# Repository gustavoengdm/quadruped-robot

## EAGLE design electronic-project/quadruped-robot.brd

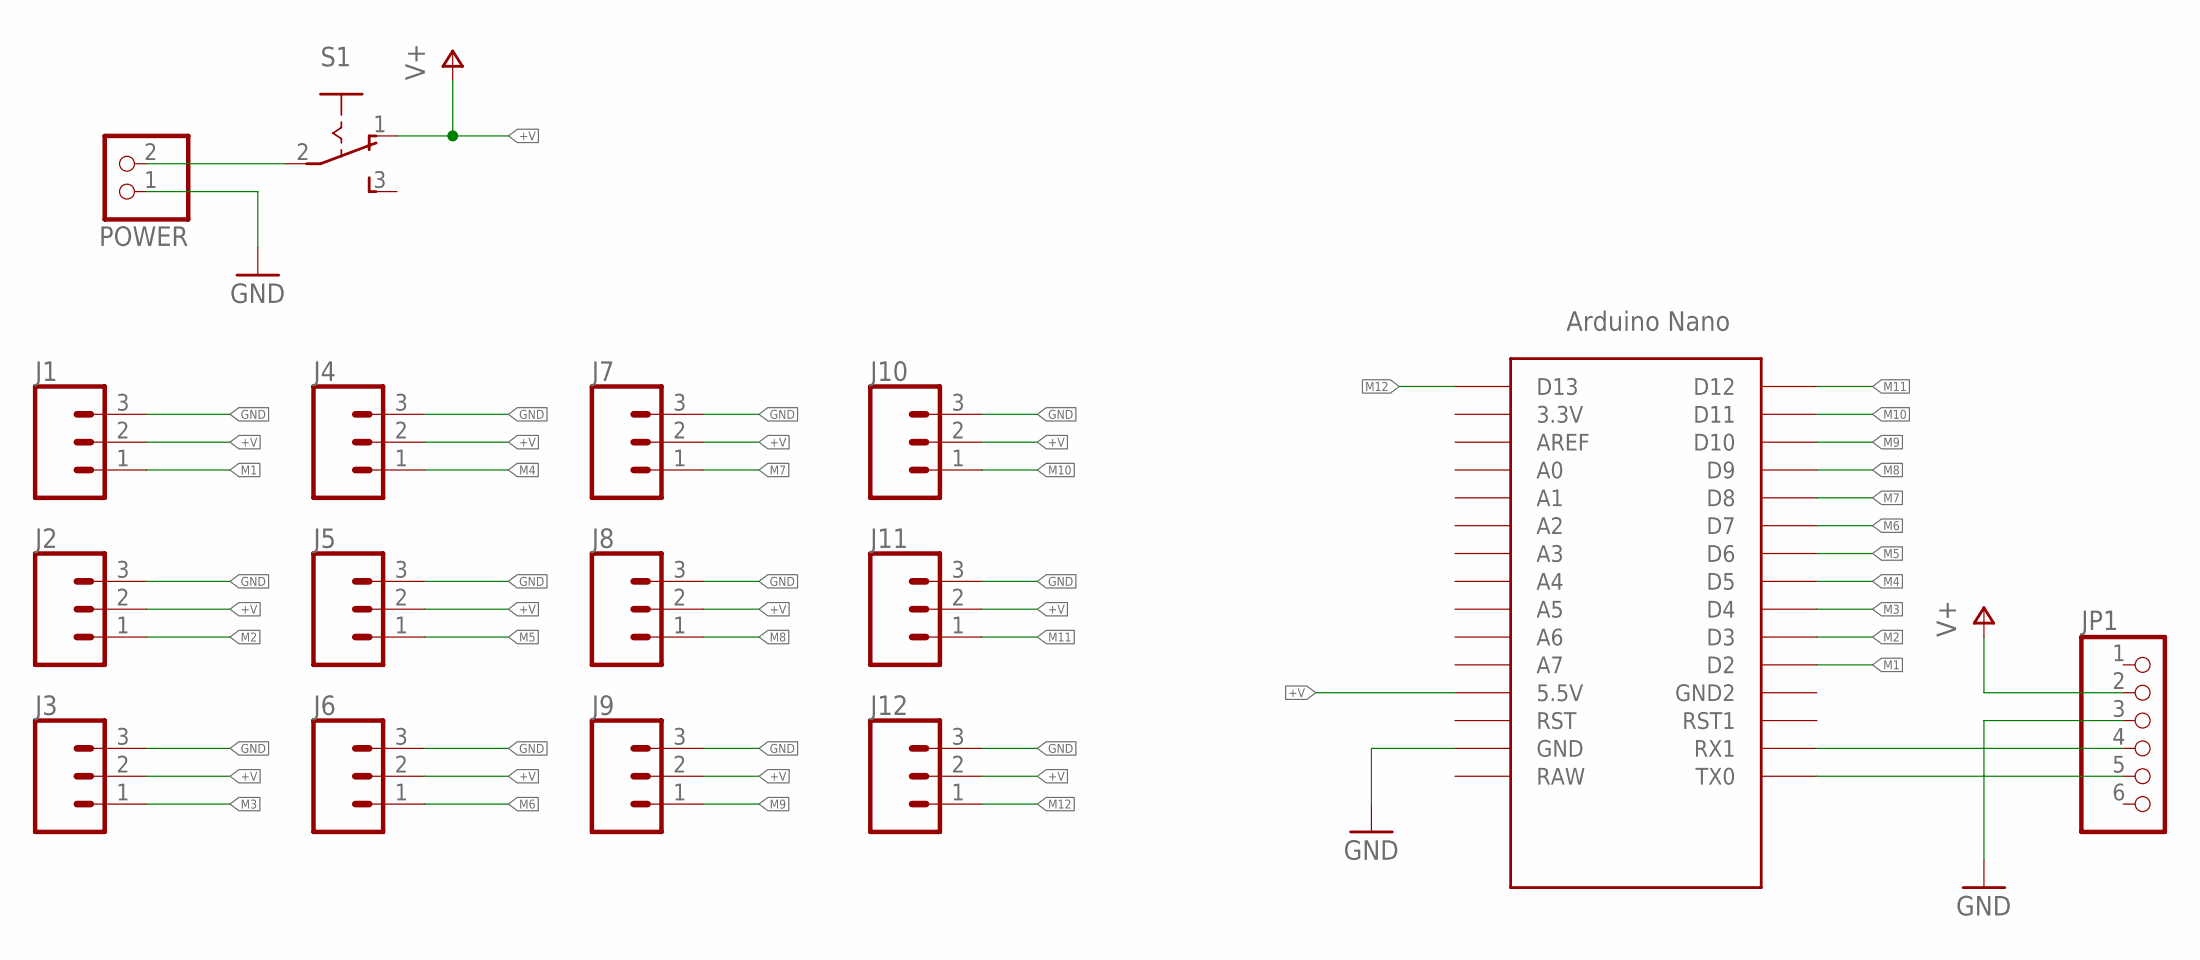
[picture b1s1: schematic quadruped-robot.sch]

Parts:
J1, J2, J3, J4, J5, J6, J7, J8, J9, J10, J11, J12: CONN_03; 1X03
JP1: PINHD-1X6; 1X06
POWER: PINHD-1X2; 1X02
S1: 255SB
U$1: NANO

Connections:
+V: J1.2, J2.2, J3.2, J4.2, J5.2, J6.2, J7.2, J8.2, J9.2, J10.2, J11.2, J12.2, JP1.2, S1.1 (O), U$1.5V (5.5V)
GND: J1.3, J2.3, J3.3, J4.3, J5.3, J6.3, J7.3, J8.3, J9.3, J10.3, J11.3, J12.3, JP1.3, POWER.1, U$1.GND
M1: J1.1, U$1.D2
M2: J2.1, U$1.D3
M3: J3.1, U$1.D4
M4: J4.1, U$1.D5
M5: J5.1, U$1.D6
M6: J6.1, U$1.D7
M7: J7.1, U$1.D8
M8: J8.1, U$1.D9
M9: J9.1, U$1.D10
M10: J10.1, U$1.D11
M11: J11.1, U$1.D12
M12: J12.1, U$1.D13
unnamed: POWER.2, S1.2
unnamed: JP1.5, U$1.TX0
unnamed: JP1.4, U$1.RX1

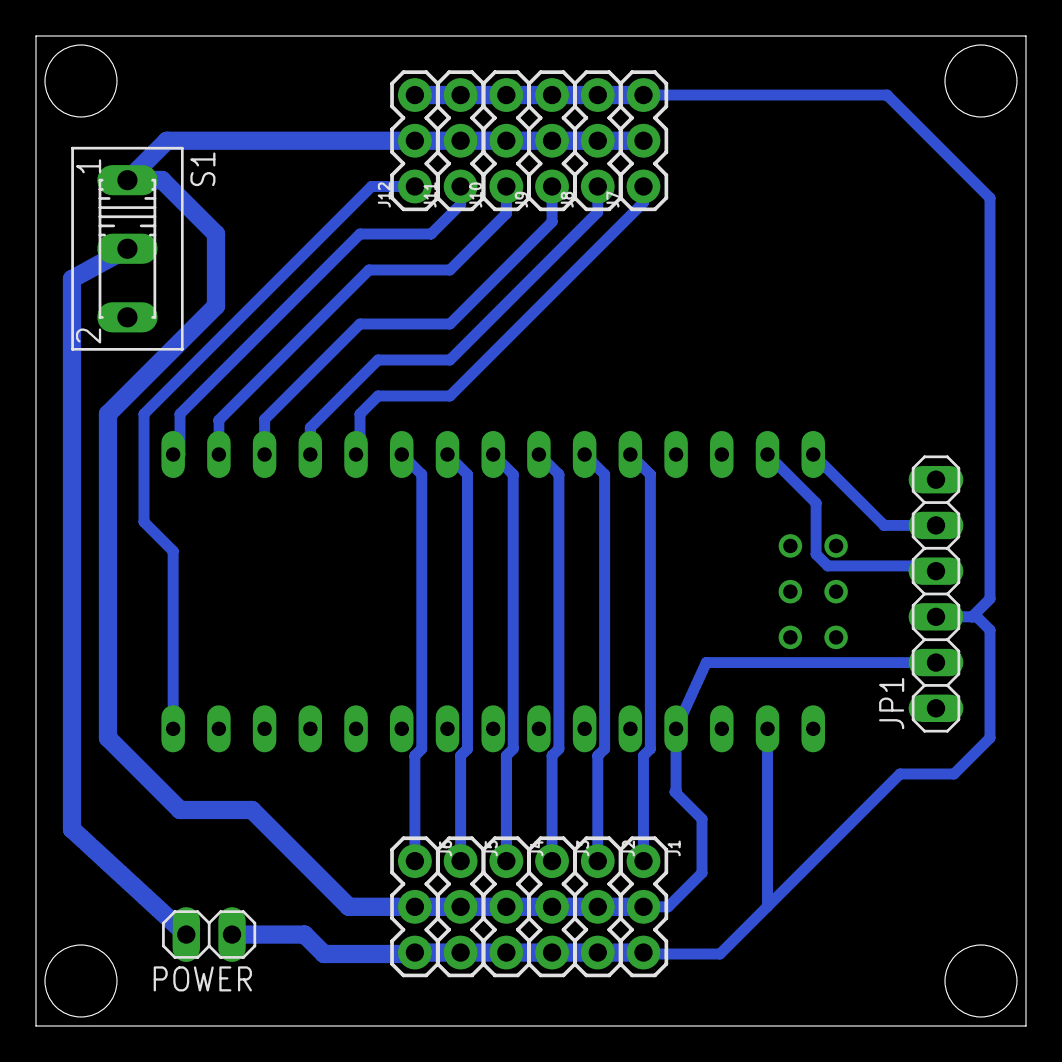
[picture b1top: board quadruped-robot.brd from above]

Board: 2 copper layers, 55.0 x 55.0 mm, 16 parts (0 on the bottom side), 17 nets.

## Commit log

2018-03-04 Init file organization and some achives.
2018-03-04 update gitignore
2018-03-06 ServoService looks better now.
2018-03-06 update usart
2018-03-08 some updates
2018-03-09 More updates. SCommand now looks good. I have implemented the selection of Function Calls.
2018-03-09 Add debug messages.
2018-03-10 update servo_service and add initial robot namespace
2018-03-12 working...
2018-04-08 add set_angle function

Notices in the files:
parts and their libraries:
SparkFun-Connectors: Licensing: Creative Commons ShareAlike 4.0 International - https://creativecommons.org/licenses/by-sa/4.0
